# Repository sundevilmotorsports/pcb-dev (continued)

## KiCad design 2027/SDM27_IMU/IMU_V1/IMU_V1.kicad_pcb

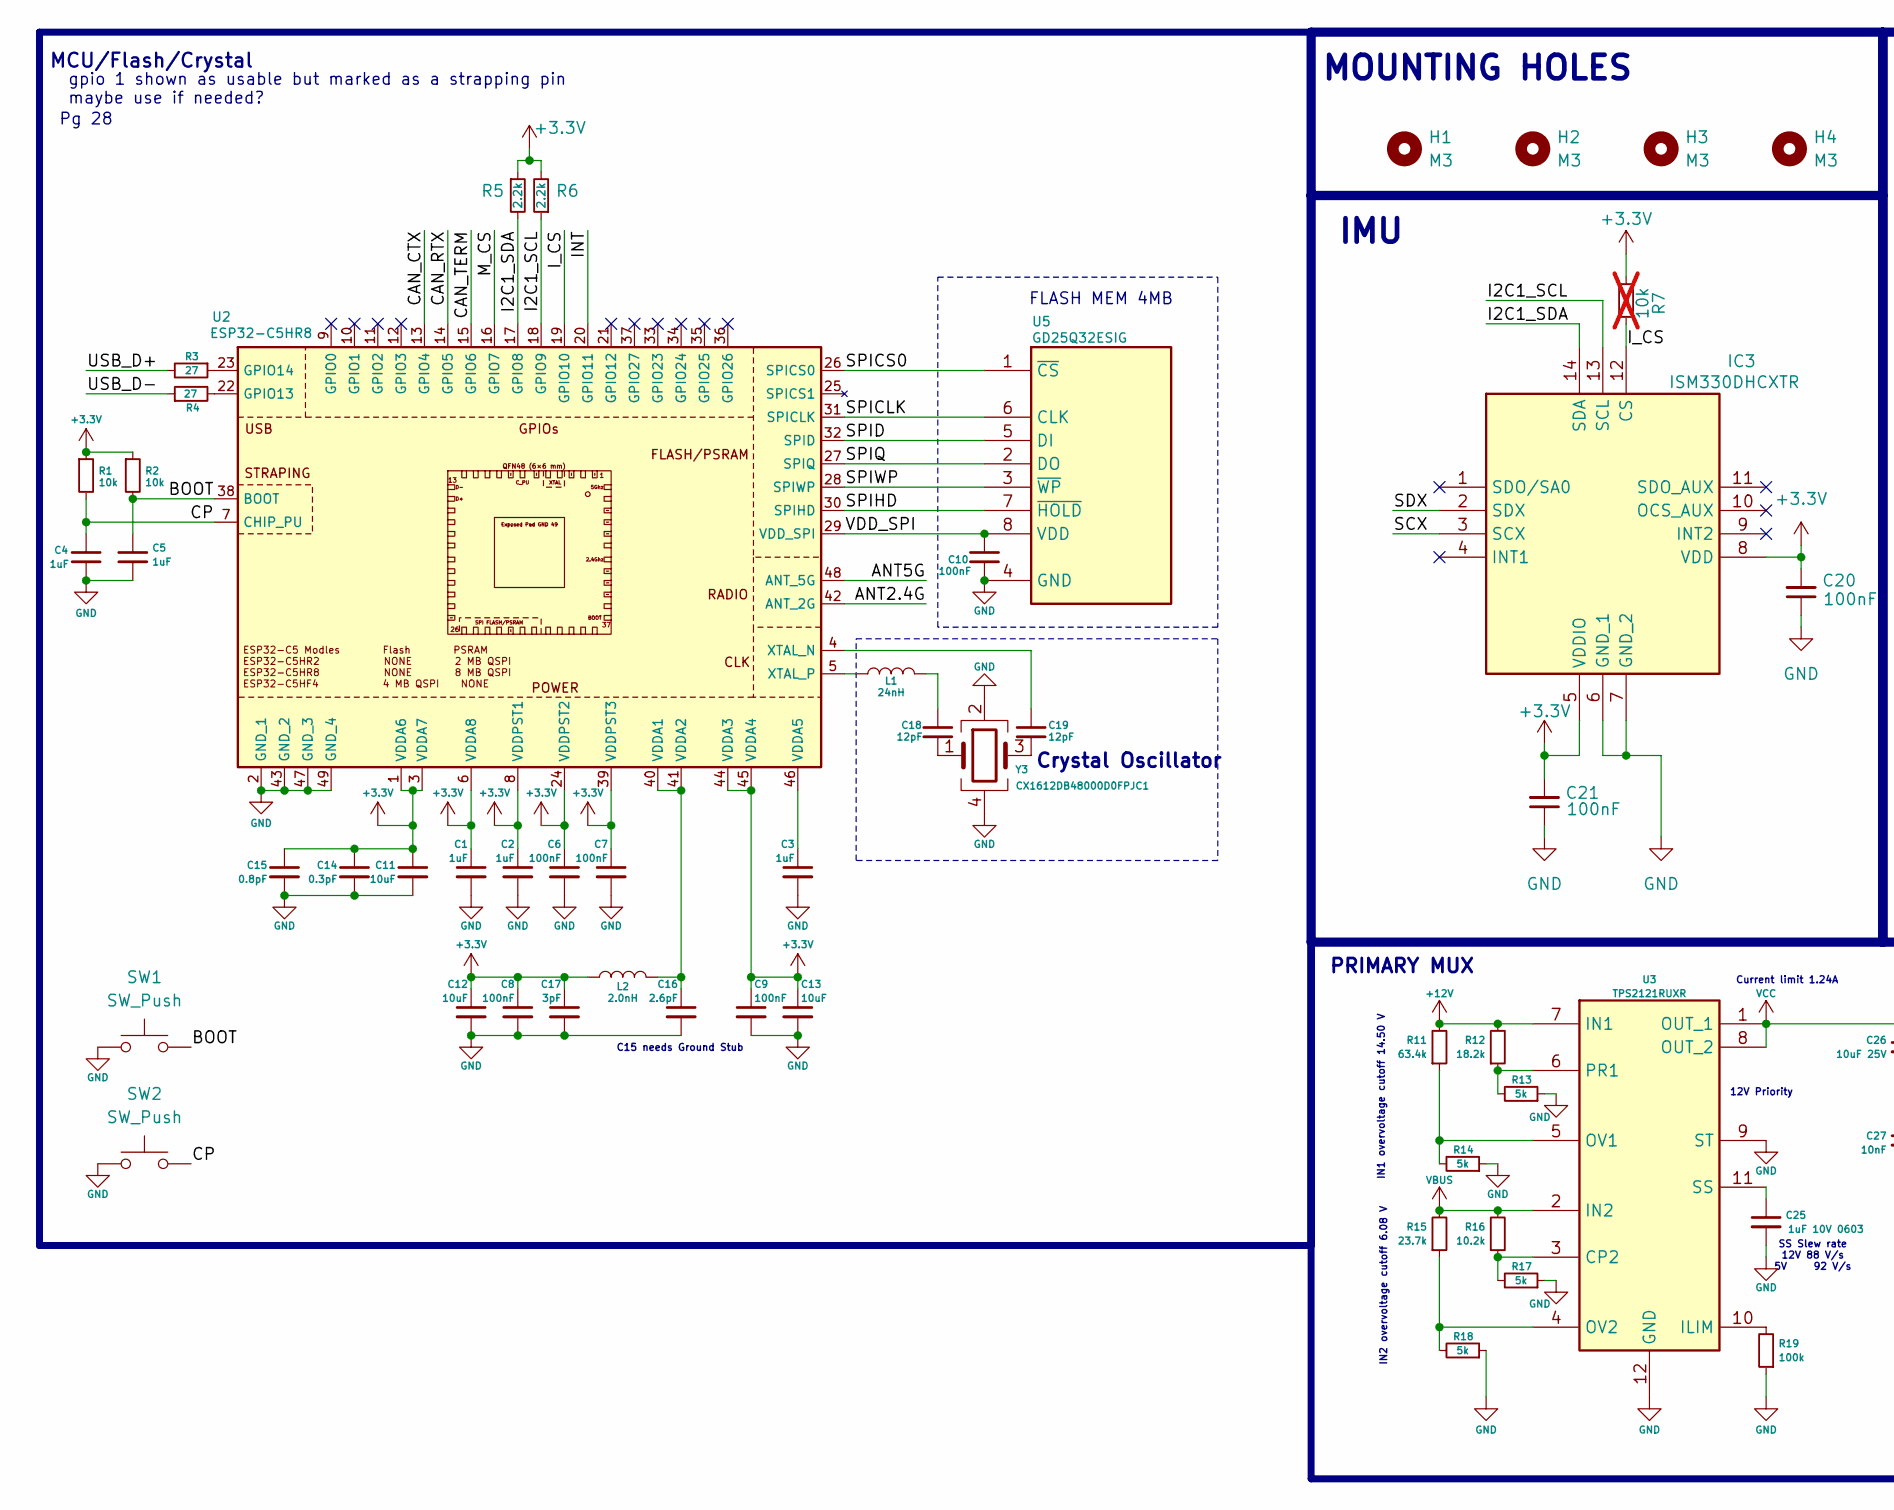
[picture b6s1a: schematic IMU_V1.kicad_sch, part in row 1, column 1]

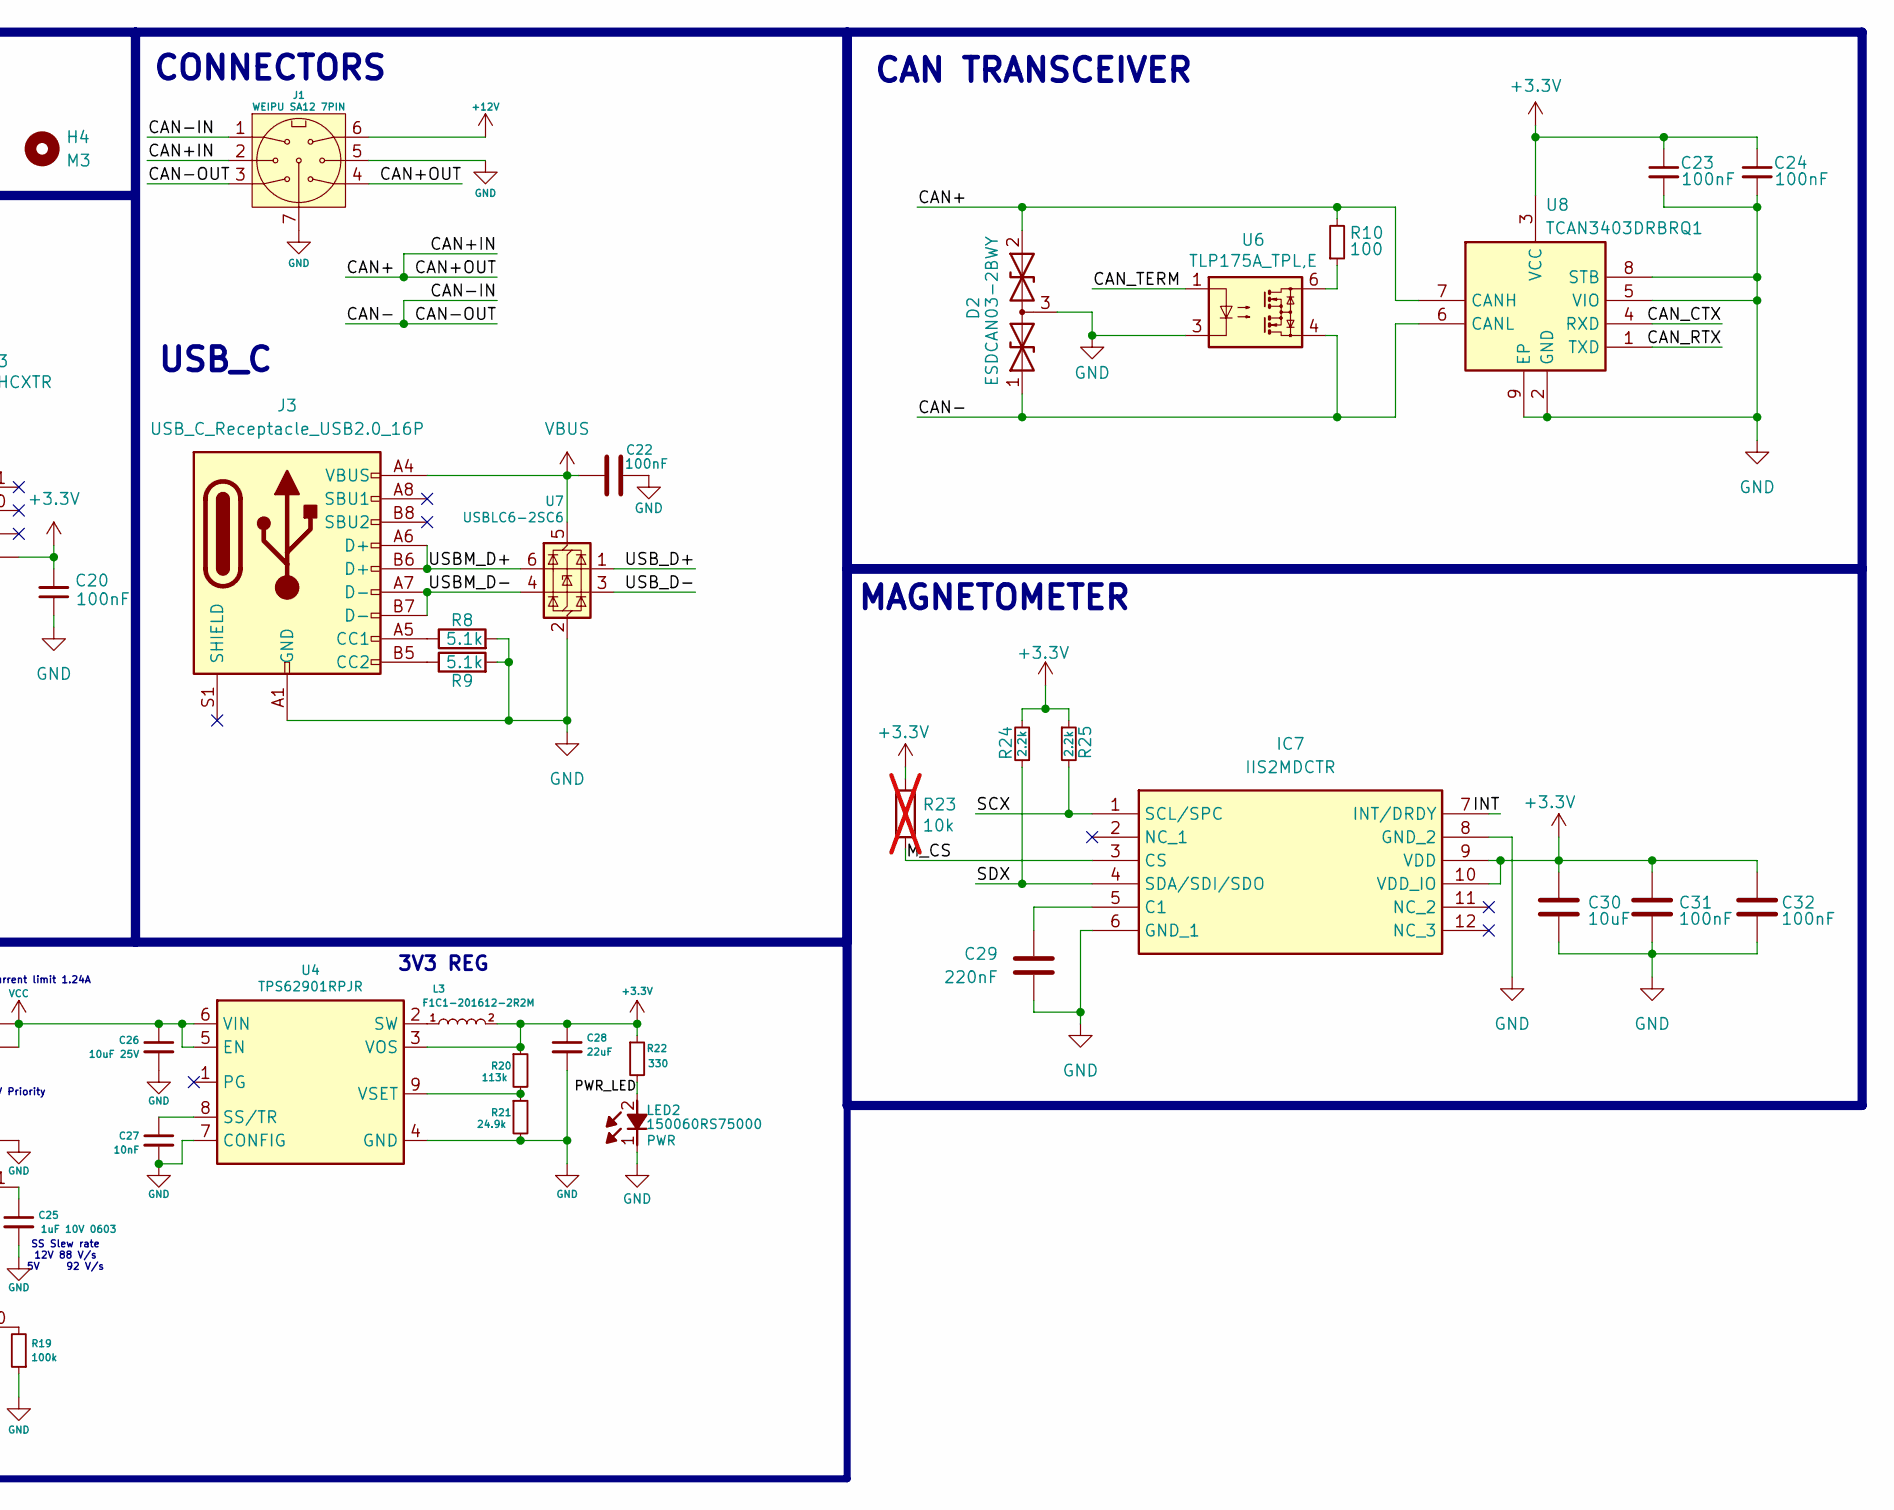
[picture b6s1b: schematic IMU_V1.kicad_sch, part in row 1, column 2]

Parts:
C1, C2, C3, C4, C5: 1uF; C_0603_1608Metric
C6, C7, C8, C9, C10, C20, C21, C22, C23, C24, C31, C32: 100nF; C_0603_1608Metric
C11, C12, C13, C30: 10uF; C_0603_1608Metric
C14: 0.3pF; C_0603_1608Metric
C15: 0.8pF; C_0603_1608Metric
C16: 2.6pF; C_0603_1608Metric
C17: 3pF; C_0603_1608Metric
C18, C19: 12pF; C_0603_1608Metric
C25: 1uF 10V 0603; C_0603_1608Metric
C26: 10uF 25V; C_0603_1608Metric
C27: 10nF; C_0603_1608Metric
C28: 22uF; C_0603_1608Metric
C29: 220nF; C_0603_1608Metric
D2: ESDCAN03-2BWY; SOT65P210X110-3N; Mouser Part Number 511-ESDCAN03-2BWY
H1, H2, H3, H4: M3; MountingHole_3.2mm_M3
IC3: ISM330DHCXTR; LSM6DS3USTR; Mouser Part Number 511-ISM330DHCXTR
IC7: IIS2MDCTR; Mouser Part Number 511-IIS2MDCTR
J1: WEIPU SA12 7PIN; JST_PH_B7B-PH-K_1x07_P2.00mm_Vertical
J3: USB_C_Receptacle_USB2.0_16P; USB_C_Receptacle_G-Switch_GT-USB-7010ASV
L1: 24nH; L_0402_1005Metric
L2: 2.0nH; L_0402_1005Metric
L3: F1C1-201612-2R2M; F1C12016122R2M; Mouser Part Number 530-F1C1-201612-2R2M
LED2: 150060RS75000; LEDC1608X80N; Mouser Part Number 710-150060RS75000
R1, R2: 10k; R_0603_1608Metric
R3, R4: 27; R_0402_1005Metric
R5, R6, R24, R25: 2.2k; R_0603_1608Metric
R7, R23: 10k; R_0603_1608Metric; not fitted
R8, R9: 5.1k; R_0603_1608Metric
R10: 100; R_0603_1608Metric
R11: 63.4k; R_0603_1608Metric
R12: 18.2k; R_0603_1608Metric
R13, R14, R17, R18: 5k; R_0603_1608Metric
R15: 23.7k; R_0603_1608Metric
R16: 10.2k; R_0603_1608Metric
R19: 100k; R_0603_1608Metric
R20: 113k; R_0603_1608Metric
R21: 24.9k; R_0603_1608Metric
R22: 330; R_0603_1608Metric
SW1, SW2: SW_Push; SW_SPST_CK_KXT3
U2: ESP32-C5HR8; QFN40P600X600X90-49N-D; Manufacturer_Part_Number ESP32-C5HR8
U3: TPS2121RUXR; Mouser Part Number 595-TPS2121RUXR
U4: TPS62901RPJR; Mouser Part Number 595-TPS62901RPJR
U5: GD25Q32ESIG; SOP-8_3.76x4.96mm_P1.27mm; Mouser Part Number 363-GD25Q32ESIG
U6: TLP175A_TPL,E; TLP266J; Mouser Part Number 757-TLP175A(TPLE
U7: USBLC6-2SC6; SOT-23-6
U8: TCAN3403DRBRQ1; SON65P300X300X100-9N-D; Manufacturer_Part_Number TCAN3403DRBRQ1; Mouser Part Number 595-TCAN3403DRBRQ1
Y3: CX1612DB48000D0FPJC1; Mouser Part Number 581-CX1612DB48D0FPJ

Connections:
+3.3V: C1.1, C2.1, C6.1, C7.1, C8.1, C9.1, C11.1, C12.1, C13.1, C14.1, C15.1, C17.1, C20.2, C21.2, C23.1, C24.1, C28.1, C30.1, C31.1, C32.1, IC3.5 (VDDIO), IC3.8 (VDD), IC7.9 (VDD), IC7.10 (VDD_IO), L2.2, L3.2, R1.1, R2.1, R5.1, R6.2, R7.2, R20.1, R22.1, R23.1, R24.2, R25.1, U2.1 (VDDA6), U2.3 (VDDA7), U2.6 (VDDA8), U2.8 (VDDPST1), U2.24 (VDDPST2), U2.39 (VDDPST3), U2.44 (VDDA3), U2.45 (VDDA4), U4.3 (VOS), U8.3 (VCC)
+12V: J1.6, R11.2, R12.2, U3.7 (IN1)
/ANT2.4G: U2.42 (ANT_2G)
/ANT5G: U2.48 (ANT_5G)
/BOOT: C5.1, R2.2, SW1.2, U2.38 (BOOT)
/CAN+: D2.2, J1.2, J1.4, R10.2, U8.7 (CANH)
/CAN-: D2.1, J1.1, J1.3, U6.4, U8.6 (CANL)
/CAN_CTX: U2.13 (GPIO4), U8.4 (RXD)
/CAN_RTX: U2.14 (GPIO5), U8.1 (TXD)
/CAN_TERM: U2.15 (GPIO6), U6.1
/CP: C4.1, R1.2, SW2.2, U2.7 (CHIP_PU)
/I2C1_SCL: IC3.13 (SCL), R6.1, U2.18 (GPIO9)
/I2C1_SDA: IC3.14 (SDA), R5.2, U2.17 (GPIO8)
/INT: IC7.7 (INT/DRDY), U2.20 (GPIO11)
/I_CS: IC3.12 (CS), R7.1, U2.19 (GPIO10)
/M_CS: IC7.3 (CS), R23.2, U2.16 (GPIO7)
/PWR_LED: LED2.2 (A), R22.2
/SCX: IC3.3 (SCX), IC7.1 (SCL/SPC), R25.2
/SDX: IC3.2 (SDX), IC7.4 (SDA/SDI/SDO), R24.1
/SPICLK: U2.31 (SPICLK), U5.6 (CLK)
/SPICS0: U2.26 (SPICS0), U5.1 (~CS)
/SPID: U2.32 (SPID), U5.5 (DI)
/SPIHD: U2.30 (SPIHD), U5.7 (~HOLD)
/SPIQ: U2.27 (SPIQ), U5.2 (DO)
/SPIWP: U2.28 (SPIWP), U5.3 (~WP)
/USBM_D+: J3.A6 (D+), J3.B6 (D+), U7.6 (I/O1)
/USBM_D-: J3.A7 (D-), J3.B7 (D-), U7.4 (I/O2)
/USB_D+: R3.2, U7.1 (I/O1)
/USB_D-: R4.1, U7.3 (I/O2)
/VDD_SPI: C10.1, U2.29 (VDD_SPI), U5.8 (VDD)
GND: C1.2, C2.2, C3.2, C4.2, C5.2, C6.2, C7.2, C8.2, C9.2, C10.2, C11.2, C12.2, C13.2, C14.2, C15.2, C16.2, C17.2, C20.1, C21.1, C22.1, C23.2, C24.2, C25.2, C26.2, C27.2, C28.2, C29.2, C30.2, C31.2, C32.2, D2.3, IC3.6 (GND_1), IC3.7 (GND_2), IC7.6 (GND_1), IC7.8 (GND_2), J1.5, J1.7, J3.A1 (GND), J3.A12 (GND), J3.B1 (GND), J3.B12 (GND), LED2.1 (K), R8.2, R9.2, R13.1, R14.1, R17.1, R18.1, R19.1, R21.2, SW1.1, SW2.1, U2.2 (GND_1), U2.43 (GND_2), U2.47 (GND_3), U2.49 (GND_4), U3.9 (ST), U3.12 (GND), U4.4 (GND), U4.7 (CONFIG), U5.4 (GND), U6.3, U7.2 (GND), U8.2 (GND), U8.5 (VIO), U8.8 (STB), U8.9 (EP), Y3.2, Y3.4
unnamed: C18.1, L1.2
unnamed: C18.2, Y3.1
unnamed: C19.2, Y3.3
unnamed: C29.1, IC7.5 (C1)
unnamed: J3.A5 (CC1), R8.1
unnamed: J3.B5 (CC2), R9.1
unnamed: R10.1, U6.6
unnamed: R4.2, U2.22 (GPIO13)
unnamed: R3.1, U2.23 (GPIO14)
unnamed: C16.1, L2.1, U2.40 (VDDA1), U2.41 (VDDA2)
unnamed: C3.1, U2.46 (VDDA5)
unnamed: C19.1, U2.4 (XTAL_N)
unnamed: L1.1, U2.5 (XTAL_P)
unnamed: R16.1, R17.2, U3.3 (CP2)
unnamed: R19.2, U3.10 (ILIM)
unnamed: R11.1, R14.2, U3.5 (OV1)
unnamed: R15.1, R18.2, U3.4 (OV2)
unnamed: R12.1, R13.2, U3.6 (PR1)
unnamed: C25.1, U3.11 (SS)
unnamed: C27.1, U4.8 (SS/TR)
unnamed: L3.1, U4.2 (SW)
unnamed: R20.2, R21.1, U4.9 (VSET)
VBUS: C22.2, J3.A4 (VBUS), J3.A9 (VBUS), J3.B4 (VBUS), J3.B9 (VBUS), R15.2, R16.2, U3.2 (IN2), U7.5 (VBUS)
VCC: C26.1, U3.1 (OUT_1), U3.8 (OUT_2), U4.5 (EN), U4.6 (VIN)

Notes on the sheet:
Crystal Oscillator
IN1 overvoltage cutoff 14.50 V
SS Slew rate 12V 88 V/s 5V 92 V/s
12V Priority
USB_C
IN2 overvoltage cutoff 6.08 V
FLASH MEM 4MB
gpio 1 shown as usable but marked as a strapping pin maybe use if needed?
Pg 28
MAGNETOMETER
CAN TRANSCEIVER
MCU/Flash/Crystal
IMU
C15 needs Ground Stub
3V3 REG
PRIMARY MUX
CONNECTORS
Current limit 1.24A
MOUNTING HOLES

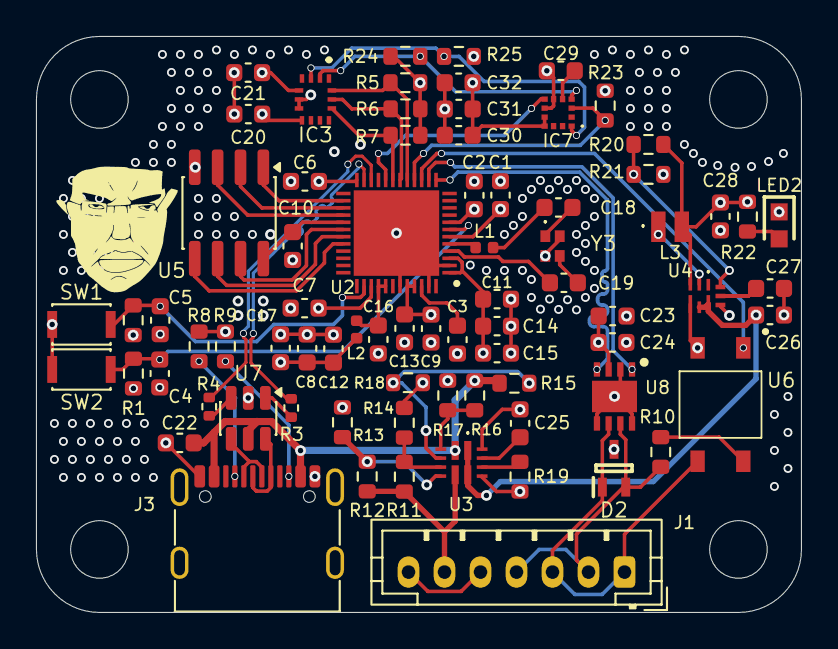
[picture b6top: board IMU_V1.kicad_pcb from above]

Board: 4 copper layers, 42.5 x 32.0 mm, 80 parts (0 on the bottom side), 53 nets.
